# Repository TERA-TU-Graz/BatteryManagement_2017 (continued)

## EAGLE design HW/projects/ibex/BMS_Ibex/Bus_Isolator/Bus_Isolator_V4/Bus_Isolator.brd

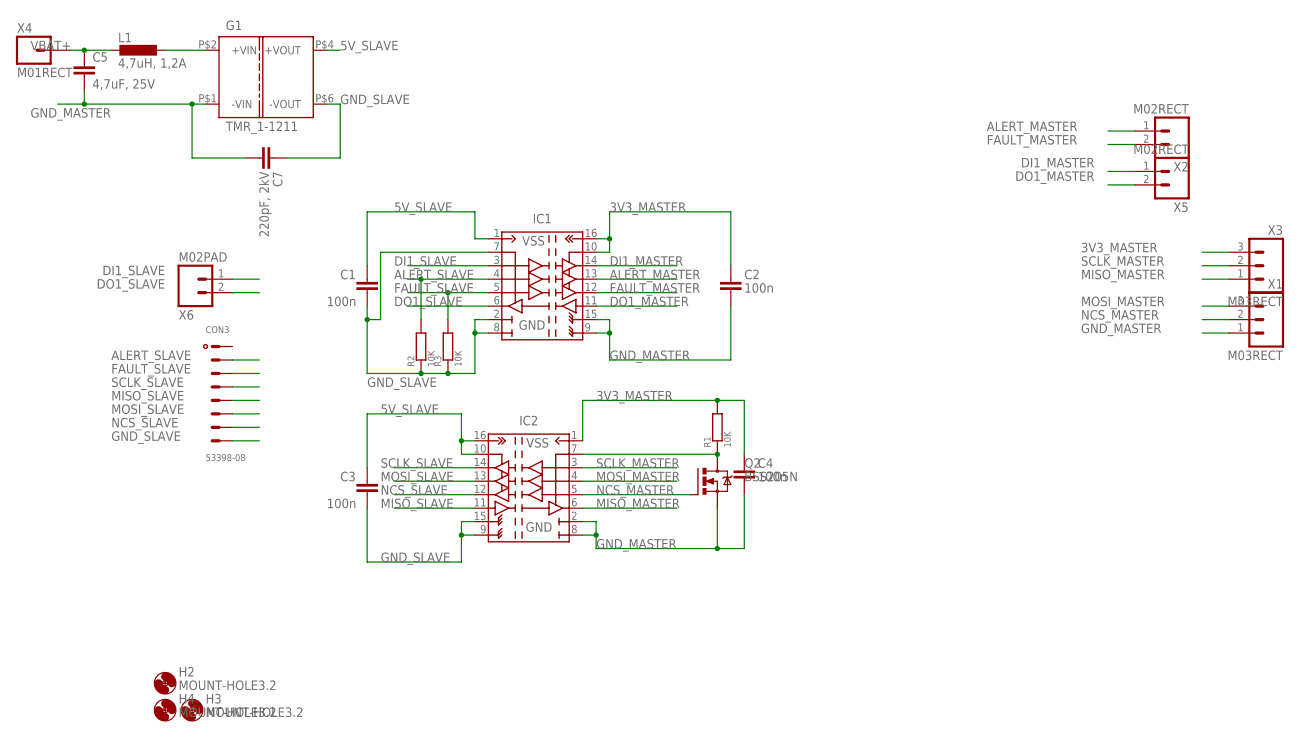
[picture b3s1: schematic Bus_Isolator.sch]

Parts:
C1, C2, C3, C4: 100n; C0805
C5: 4,7uF, 25V; C0805
C7: 220pF, 2kV; C1210_HV
CON3: 53398-08
G1: TMR_1-1211; TMR_1-??1?
H2, H3, H4: MOUNT-HOLE3.2; 3,2
IC1, IC2: ISO7241; R-PDSO-G16
L1: 4,7uH, 1,2A; L3225M
Q2: BSS205N; SOT23
R1: 10K; R0603
R2, R3: 10K; R0805
X1, X3: M03RECT; 1X03_RECT
X2, X5: M02RECT; 1X02_RECT
X4: M01RECT; 1X01_RECT
X6: M02PAD; 1X02

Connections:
3V3_MASTER: C2.2, C4.2, IC1.10 (EN2), IC1.16 (VCC2), IC2.1 (VCC1), R1.2, X3.3
5V_SLAVE: C1.2, C3.2, G1.P$4 (+VOUT), IC1.1 (VCC1), IC2.10 (EN2), IC2.16 (VCC2)
ALERT_MASTER: IC1.13 (OUT_B), X2.1
ALERT_SLAVE: CON3.2, IC1.4 (IN_B), R2.2
DI1_MASTER: IC1.14 (OUT_A), X5.1
DI1_SLAVE: IC1.3 (IN_A), X6.1
DO1_MASTER: IC1.11 (IN_D), X5.2
DO1_SLAVE: IC1.6 (OUT_D), X6.2
FAULT_MASTER: IC1.12 (OUT_C), X2.2
FAULT_SLAVE: CON3.3, IC1.5 (IN_C), R3.2
GND_MASTER: C2.1, C4.1, C5.2, C7.P$1 (1), G1.P$1 (-VIN), IC1.9 (GND22), IC1.15 (GND21), IC2.2 (GND11), IC2.8 (GND12), Q2.2 (S), X1.1
GND_SLAVE: C1.1, C3.1, C7.P$2 (2), CON3.8, G1.P$6 (-VOUT), IC1.2 (GND11), IC1.7 (EN1), IC1.8 (GND12), IC2.9 (GND22), IC2.15 (GND21), R2.1, R3.1
MISO_MASTER: IC2.6 (OUT_D), X3.1
MISO_SLAVE: CON3.5, IC2.11 (IN_D)
MOSI_MASTER: IC2.4 (IN_B), X1.3
MOSI_SLAVE: CON3.6, IC2.13 (OUT_B)
unnamed: IC2.7 (EN1), Q2.3 (D), R1.1
unnamed: G1.P$2 (+VIN), L1.1
NCS_MASTER: IC2.5 (IN_C), Q2.1 (G), X1.2
NCS_SLAVE: CON3.7, IC2.12 (OUT_C)
SCLK_MASTER: IC2.3 (IN_A), X3.2
SCLK_SLAVE: CON3.4, IC2.14 (OUT_A)
VBAT+: C5.1, L1.2, X4.1

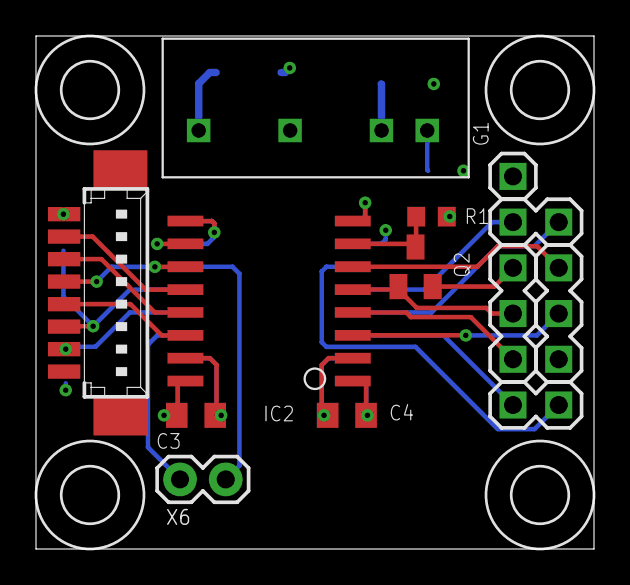
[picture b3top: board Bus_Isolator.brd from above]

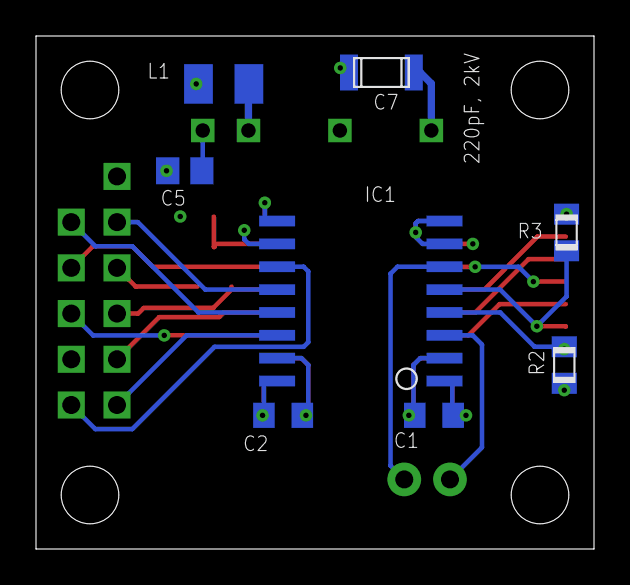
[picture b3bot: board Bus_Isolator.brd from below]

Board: 4 copper layers, 31.0 x 28.5 mm, 25 parts (8 on the bottom side), 23 nets.

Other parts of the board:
H1: MOUNT-HOLE3.2; 3,2

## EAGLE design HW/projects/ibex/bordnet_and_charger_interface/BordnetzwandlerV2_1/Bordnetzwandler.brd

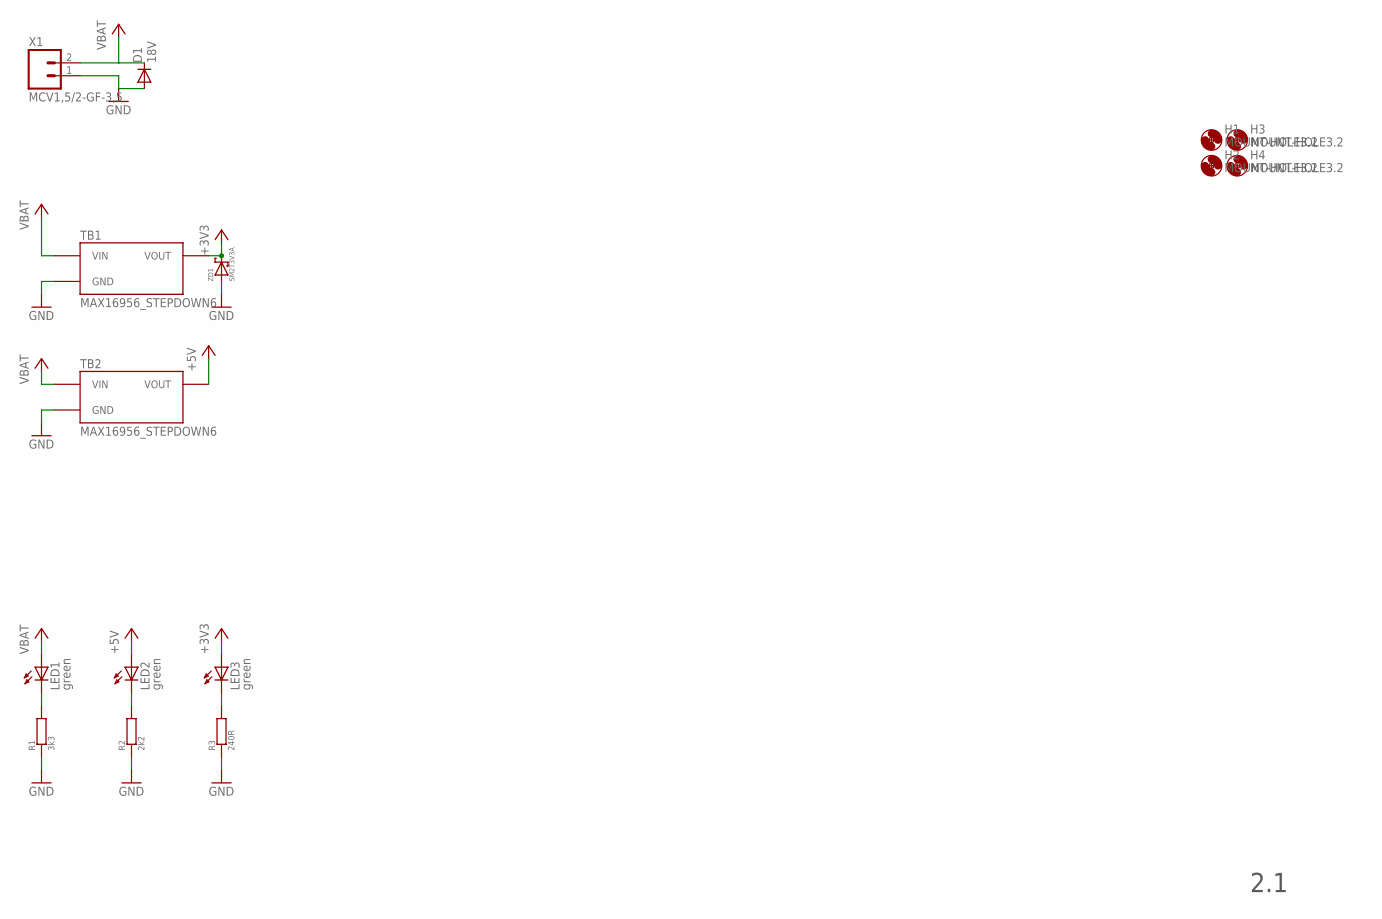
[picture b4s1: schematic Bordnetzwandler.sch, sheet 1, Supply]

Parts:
D1: 18V; DO214AA
H1, H2, H3, H4: MOUNT-HOLE3.2; 3,2
LED1, LED2, LED3: green; CHIP-LED0805
R1: 3k3; R0805
R2: 2k2; R0805
R3: 240R; R0805
TB1, TB2: MAX16956_STEPDOWN6
X1: MCV1,5/2-GF-3,5
ZD1: SM2T3V3A

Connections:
+3V3: LED3.A, TB1.VOUT, ZD1.P$2; also elsewhere on the board
+5V: LED2.A, TB2.VOUT; also elsewhere on the board
GND: D1.A, R1.1, R2.1, R3.1, TB1.GND, TB1.GND2 (GND), TB2.GND, TB2.GND2 (GND), X1.1, ZD1.P$1, ZD1.P$11; also elsewhere on the board
unnamed: LED2.C, R2.2
unnamed: LED3.C, R3.2
unnamed: LED1.C, R1.2
VBAT: D1.C, LED1.A, TB1.VIN, TB2.VIN, X1.2; also elsewhere on the board

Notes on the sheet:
2.1

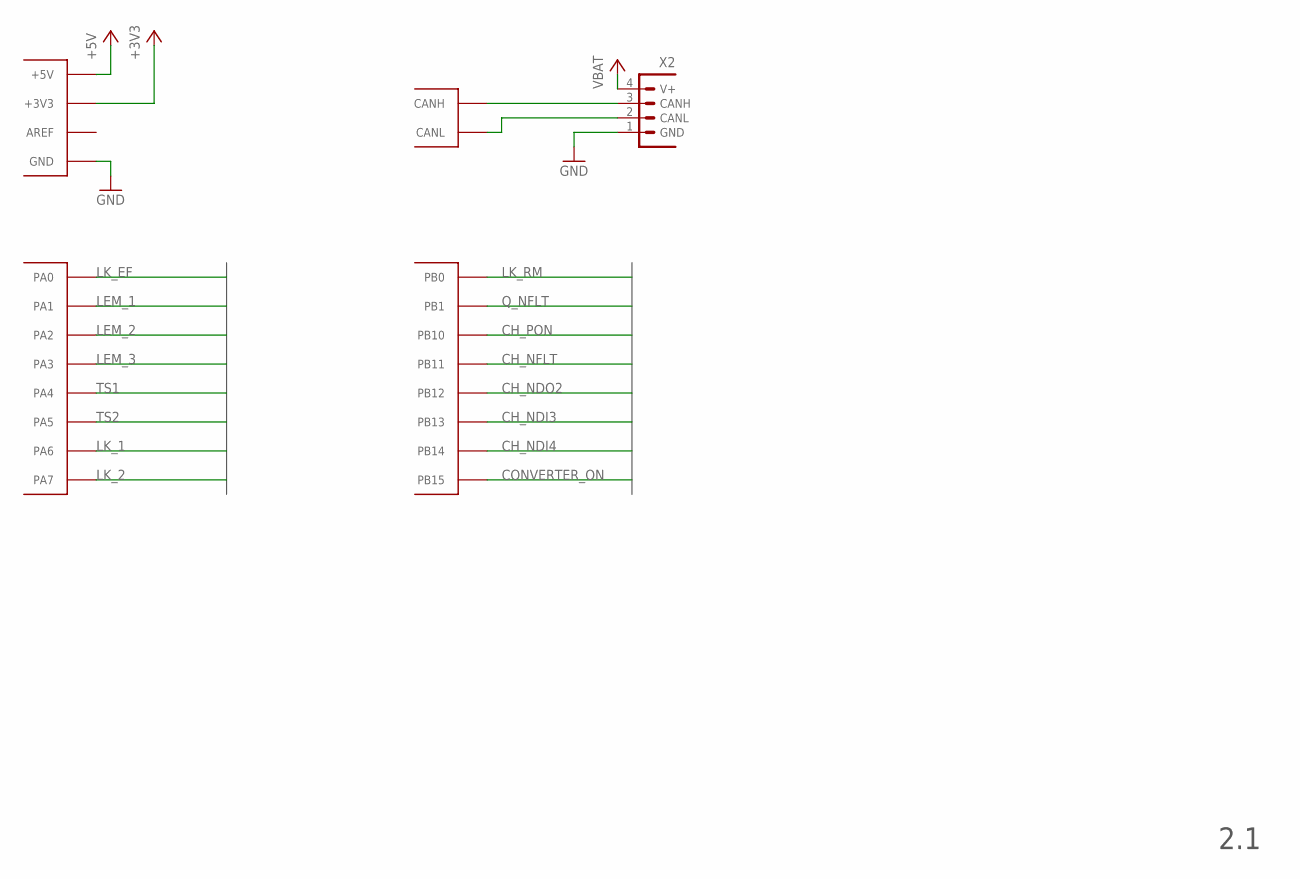
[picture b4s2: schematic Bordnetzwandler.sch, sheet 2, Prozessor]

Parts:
CANIO_1: STM32F103XX_CAN-IO-EXPANDER; STM32F103XX_CANIO-EXPANDER
X2: CIOC_4-1-FV-A_CAN-BELEGUNG; CIOC_4-1-FV

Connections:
+3V3: CANIO_1.VCC (+3V3); also elsewhere on the board
+5V: CANIO_1.+5V; also elsewhere on the board
CAN1_H: CANIO_1.CANH, X2.3 (CANH)
CAN1_L: CANIO_1.CANL, X2.2 (CANL)
CH_NDI3: CANIO_1.PB13; also elsewhere on the board
CH_NDI4: CANIO_1.PB14; also elsewhere on the board
CH_NDO2: CANIO_1.PB12; also elsewhere on the board
CH_NFLT: CANIO_1.PB11; also elsewhere on the board
CH_PON: CANIO_1.PB10; also elsewhere on the board
CONVERTER_ON: CANIO_1.PB15; also elsewhere on the board
GND: CANIO_1.GND1 (GND), X2.1 (GND); also elsewhere on the board
LEM_1: CANIO_1.PA1; also elsewhere on the board
LEM_2: CANIO_1.PA2; also elsewhere on the board
LEM_3: CANIO_1.PA3; also elsewhere on the board
LK_1: CANIO_1.PA6; also elsewhere on the board
LK_2: CANIO_1.PA7; also elsewhere on the board
LK_EF: CANIO_1.PA0; also elsewhere on the board
LK_RM: CANIO_1.PB0; also elsewhere on the board
Q_NFLT: CANIO_1.PB1; also elsewhere on the board
TS1: CANIO_1.PA4; also elsewhere on the board
TS2: CANIO_1.PA5; also elsewhere on the board
VBAT: X2.4 (V+); also elsewhere on the board

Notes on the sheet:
2.1

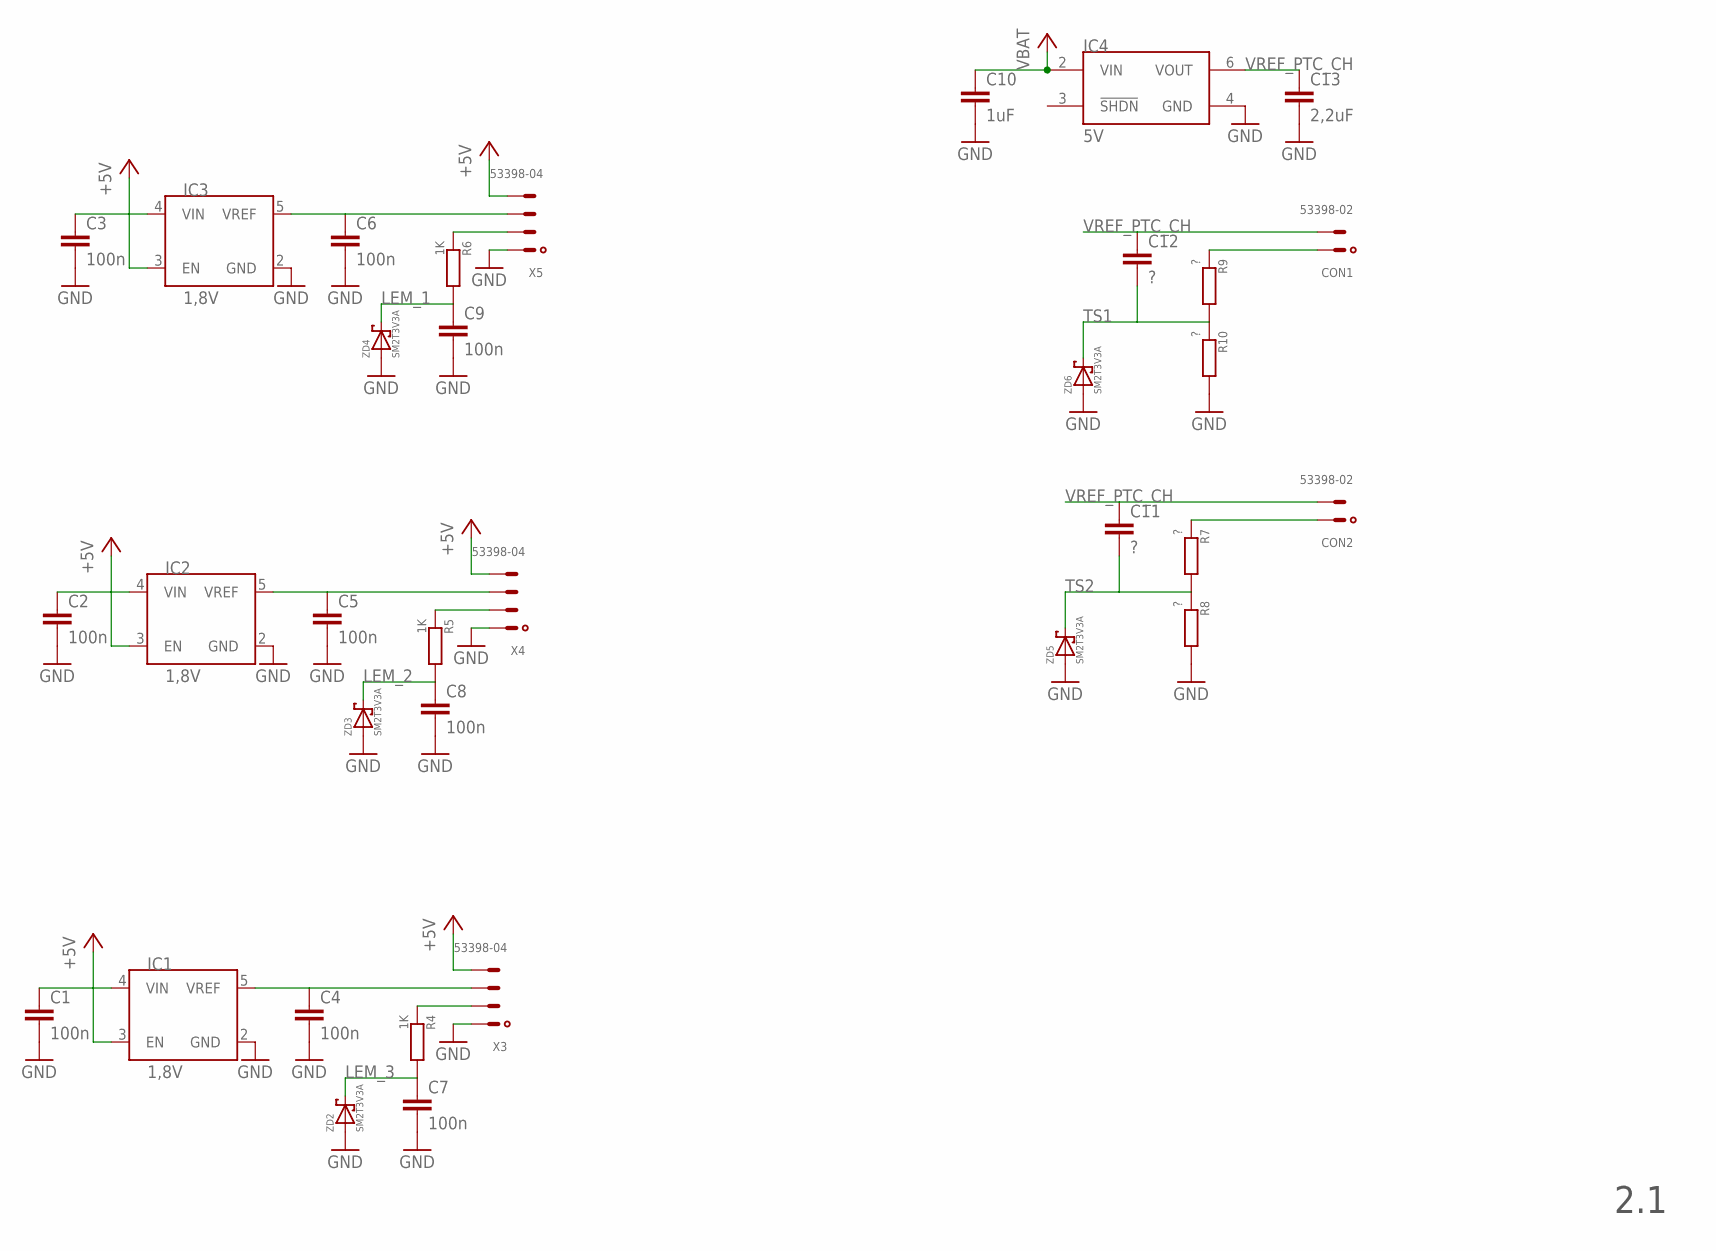
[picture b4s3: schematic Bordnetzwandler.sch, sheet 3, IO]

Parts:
C1, C2, C3, C4, C5, C6, C7, C8, C9: 100n; C0805
C10: 1uF; C0805
C11, C12: ?; C0805
C13: 2,2uF; C0805
CON1, CON2: 53398-02
IC1, IC2, IC3: 1,8V; SOT23-5L
IC4: 5V; SO08
R4, R5, R6: 1K; R0805
R7, R8, R9, R10: ?; R0805
X3, X4, X5: 53398-04
ZD2, ZD3, ZD4, ZD5, ZD6: SM2T3V3A

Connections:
+5V: C1.1, C2.1, C3.1, IC1.3 (EN), IC1.4 (VIN), IC2.3 (EN), IC2.4 (VIN), IC3.3 (EN), IC3.4 (VIN), X3.4, X4.4, X5.4; also elsewhere on the board
GND: C1.2, C2.2, C3.2, C4.2, C5.2, C6.2, C7.2, C8.2, C9.2, C10.2, C13.2, IC1.2 (GND), IC2.2 (GND), IC3.2 (GND), IC4.4 (GND), R8.2, R10.2, X3.1, X4.1, X5.1, ZD2.P$1, ZD2.P$11, ZD3.P$1, ZD3.P$11, ZD4.P$1, ZD4.P$11, ZD5.P$1, ZD5.P$11, ZD6.P$1, ZD6.P$11; also elsewhere on the board
LEM_1: C9.1, R6.2, ZD4.P$2; also elsewhere on the board
LEM_2: C8.1, R5.2, ZD3.P$2; also elsewhere on the board
LEM_3: C7.1, R4.2, ZD2.P$2; also elsewhere on the board
unnamed: C4.1, IC1.5 (VREF), X3.3
unnamed: R6.1, X5.2
unnamed: C5.1, IC2.5 (VREF), X4.3
unnamed: CON1.1, R9.1
unnamed: R5.1, X4.2
unnamed: C6.1, IC3.5 (VREF), X5.3
unnamed: R4.1, X3.2
unnamed: CON2.1, R7.1
TS1: C12.2, R9.2, R10.1, ZD6.P$2; also elsewhere on the board
TS2: C11.2, R7.2, R8.1, ZD5.P$2; also elsewhere on the board
VBAT: C10.1, IC4.2 (VIN); also elsewhere on the board
VREF_PTC_CH: C11.1, C12.1, C13.1, CON1.2, CON2.2, IC4.6 (VOUT)

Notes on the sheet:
2.1

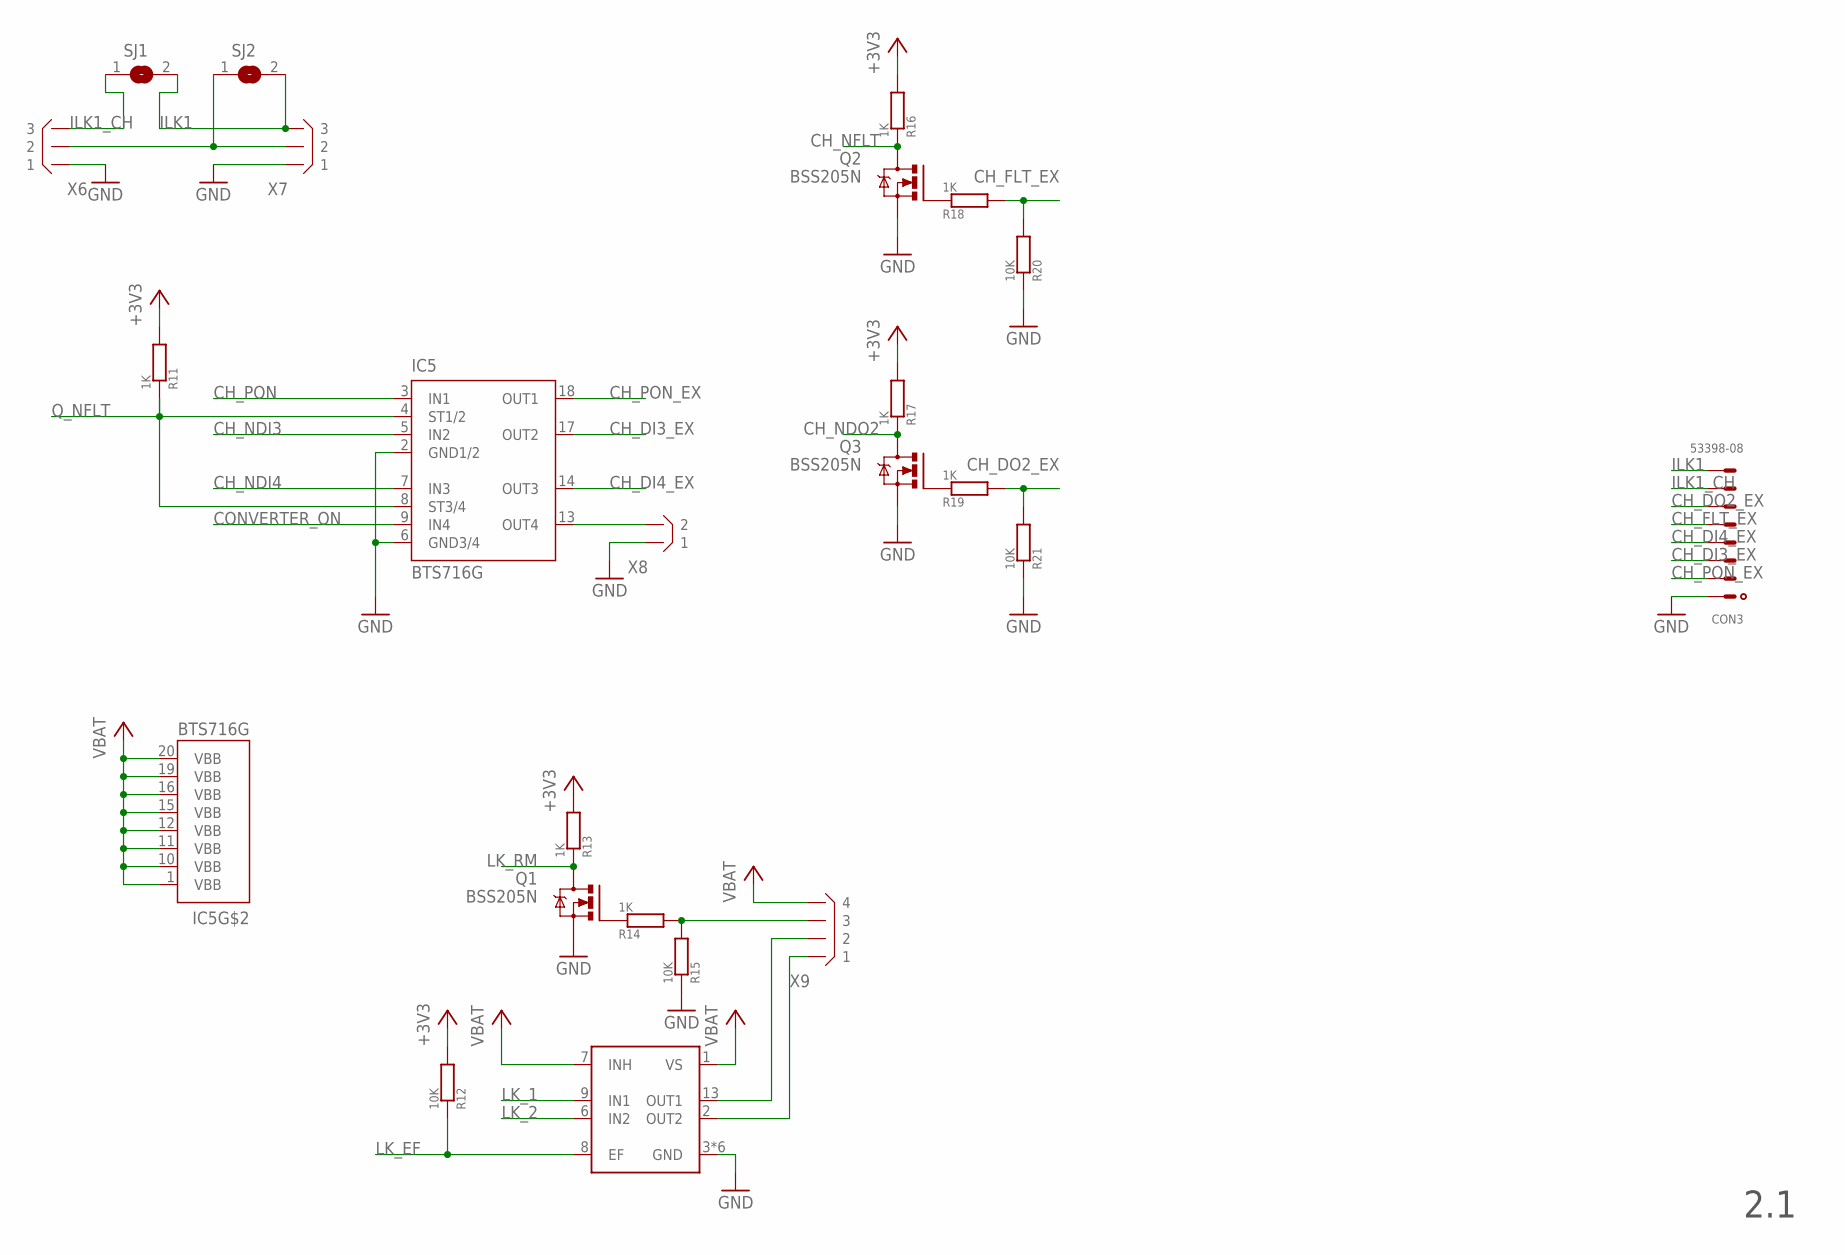
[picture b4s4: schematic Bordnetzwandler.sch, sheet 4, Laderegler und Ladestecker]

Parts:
CON3: 53398-08
IC5: BTS716G; PG-DSO-20
IC6: TLE4207GN; INF-PG-DSO-14-22_N_1PRIMARY
Q1, Q2, Q3: BSS205N; SOT23
R11, R16, R17, R18, R19: 1K; R0603
R12, R15: 10K; R0805
R13, R14: 1K; R0805
R20, R21: 10K; R0603
SJ1, SJ2: SJ
X6, X7: B3B-XH
X8: B2B-XH
X9: B4B-XH

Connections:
+3V3: R11.2, R12.2, R13.2, R16.2, R17.2; also elsewhere on the board
CH_DI3_EX: CON3.3, IC5.17 (OUT2)
CH_DI4_EX: CON3.4, IC5.14 (OUT3)
CH_DO2_EX: CON3.6, R19.2, R21.2
CH_FLT_EX: CON3.5, R18.2, R20.2
CH_NDI3: IC5.5 (IN2); also elsewhere on the board
CH_NDI4: IC5.7 (IN3); also elsewhere on the board
CH_NDO2: Q3.3 (D), R17.1; also elsewhere on the board
CH_NFLT: Q2.3 (D), R16.1; also elsewhere on the board
CH_PON: IC5.3 (IN1); also elsewhere on the board
CH_PON_EX: CON3.2, IC5.18 (OUT1)
CONVERTER_ON: IC5.9 (IN4); also elsewhere on the board
GND: CON3.1, IC5.2 (GND1/2), IC5.6 (GND3/4), IC6.3 (GND), IC6.4 (GND), IC6.5 (GND), IC6.10 (GND), IC6.11 (GND), IC6.12 (GND), Q1.2 (S), Q2.2 (S), Q3.2 (S), R15.1, R20.1, R21.1, X6.P$1 (1), X7.P$1 (1), X8.P$1 (1); also elsewhere on the board
ILK1: CON3.8, SJ1.2, SJ2.2, X7.P$3 (3)
ILK1_CH: CON3.7, SJ1.1, X6.P$3 (3)
ILK2: SJ2.1, X6.P$2 (2), X7.P$2 (2)
LK_1: IC6.9 (IN1); also elsewhere on the board
LK_2: IC6.6 (IN2); also elsewhere on the board
LK_EF: IC6.8 (EF), R12.1; also elsewhere on the board
LK_RM: Q1.3 (D), R13.1; also elsewhere on the board
unnamed: IC5.13 (OUT4), X8.P$2 (2)
unnamed: Q3.1 (G), R19.1
unnamed: Q1.1 (G), R14.1
unnamed: R14.2, R15.2, X9.P$3 (3)
unnamed: IC6.13 (OUT1), X9.P$2 (2)
unnamed: IC6.2 (OUT2), X9.P$1 (1)
unnamed: Q2.1 (G), R18.1
Q_NFLT: IC5.4 (ST1/2), IC5.8 (ST3/4), R11.1; also elsewhere on the board
VBAT: IC5.1 (VBB), IC5.10 (VBB), IC5.11 (VBB), IC5.12 (VBB), IC5.15 (VBB), IC5.16 (VBB), IC5.19 (VBB), IC5.20 (VBB), IC6.1 (VS), IC6.7 (INH), X9.P$4 (4); also elsewhere on the board

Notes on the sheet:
2.1

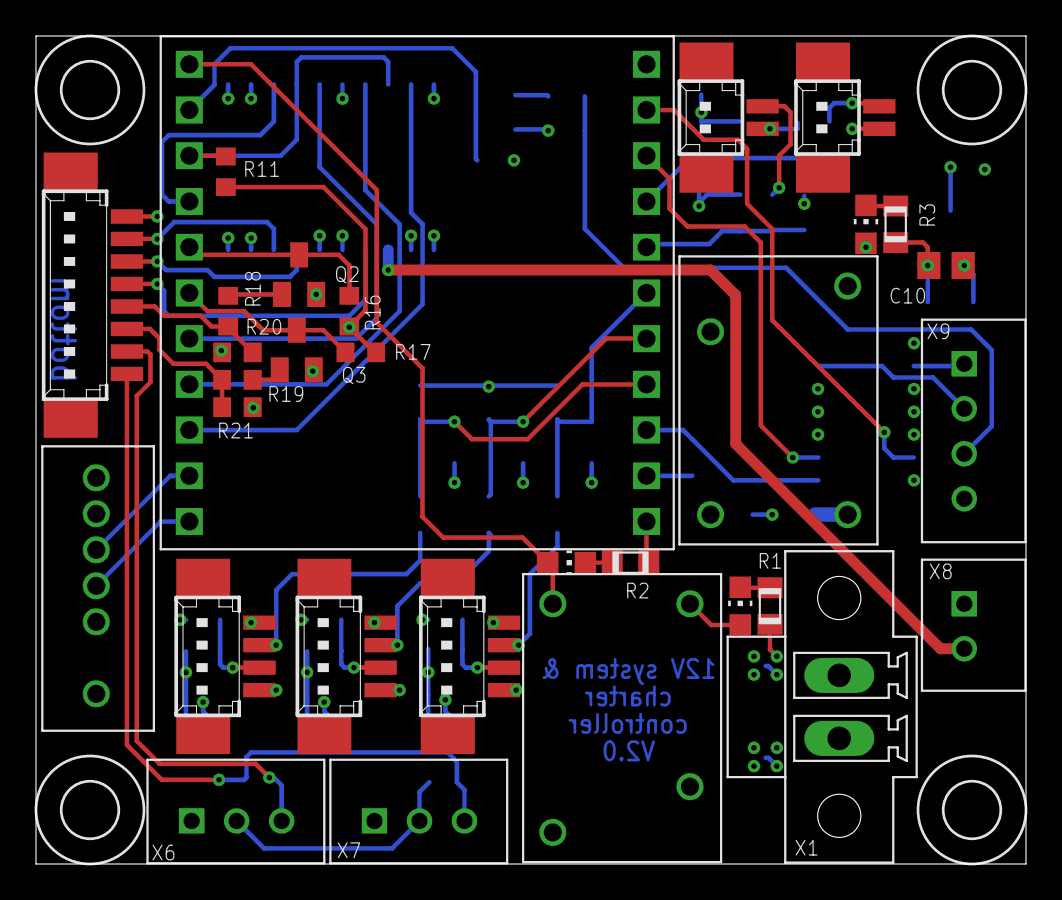
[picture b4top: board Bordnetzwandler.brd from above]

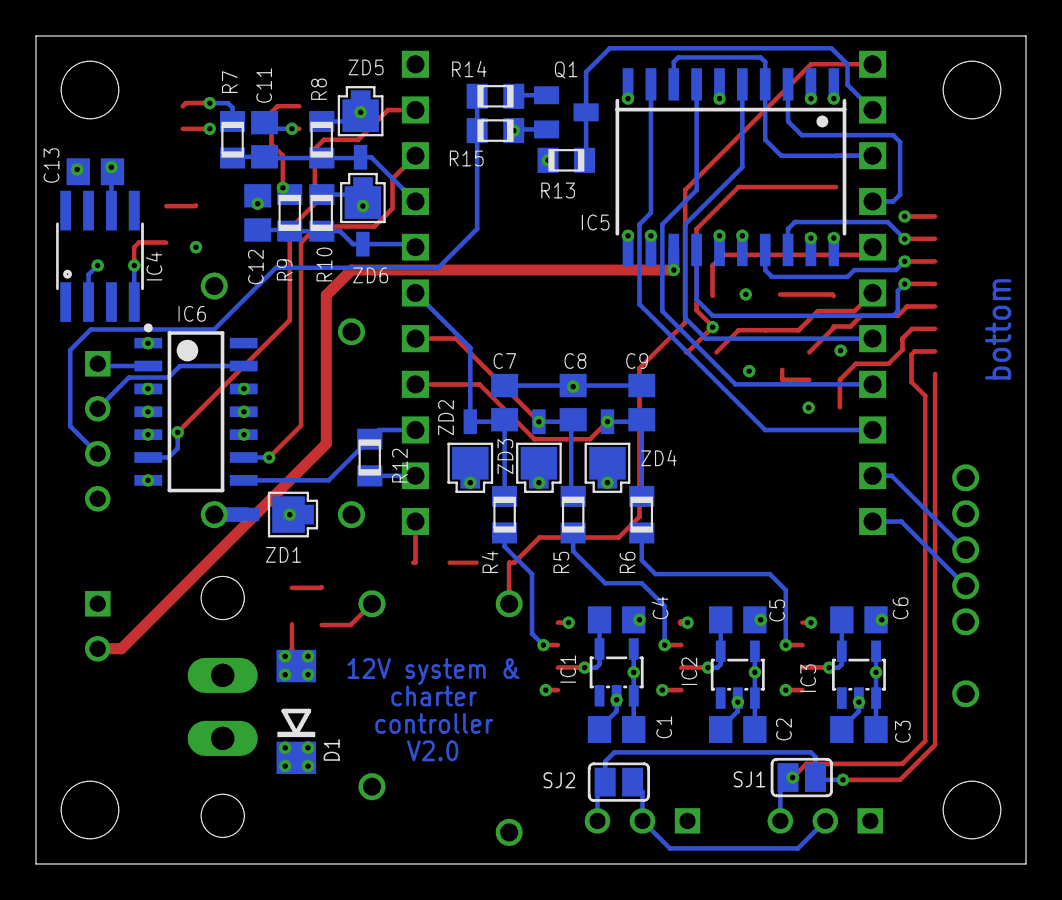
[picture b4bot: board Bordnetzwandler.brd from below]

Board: 4 copper layers, 55.0 x 46.0 mm, 74 parts (39 on the bottom side), 49 nets.

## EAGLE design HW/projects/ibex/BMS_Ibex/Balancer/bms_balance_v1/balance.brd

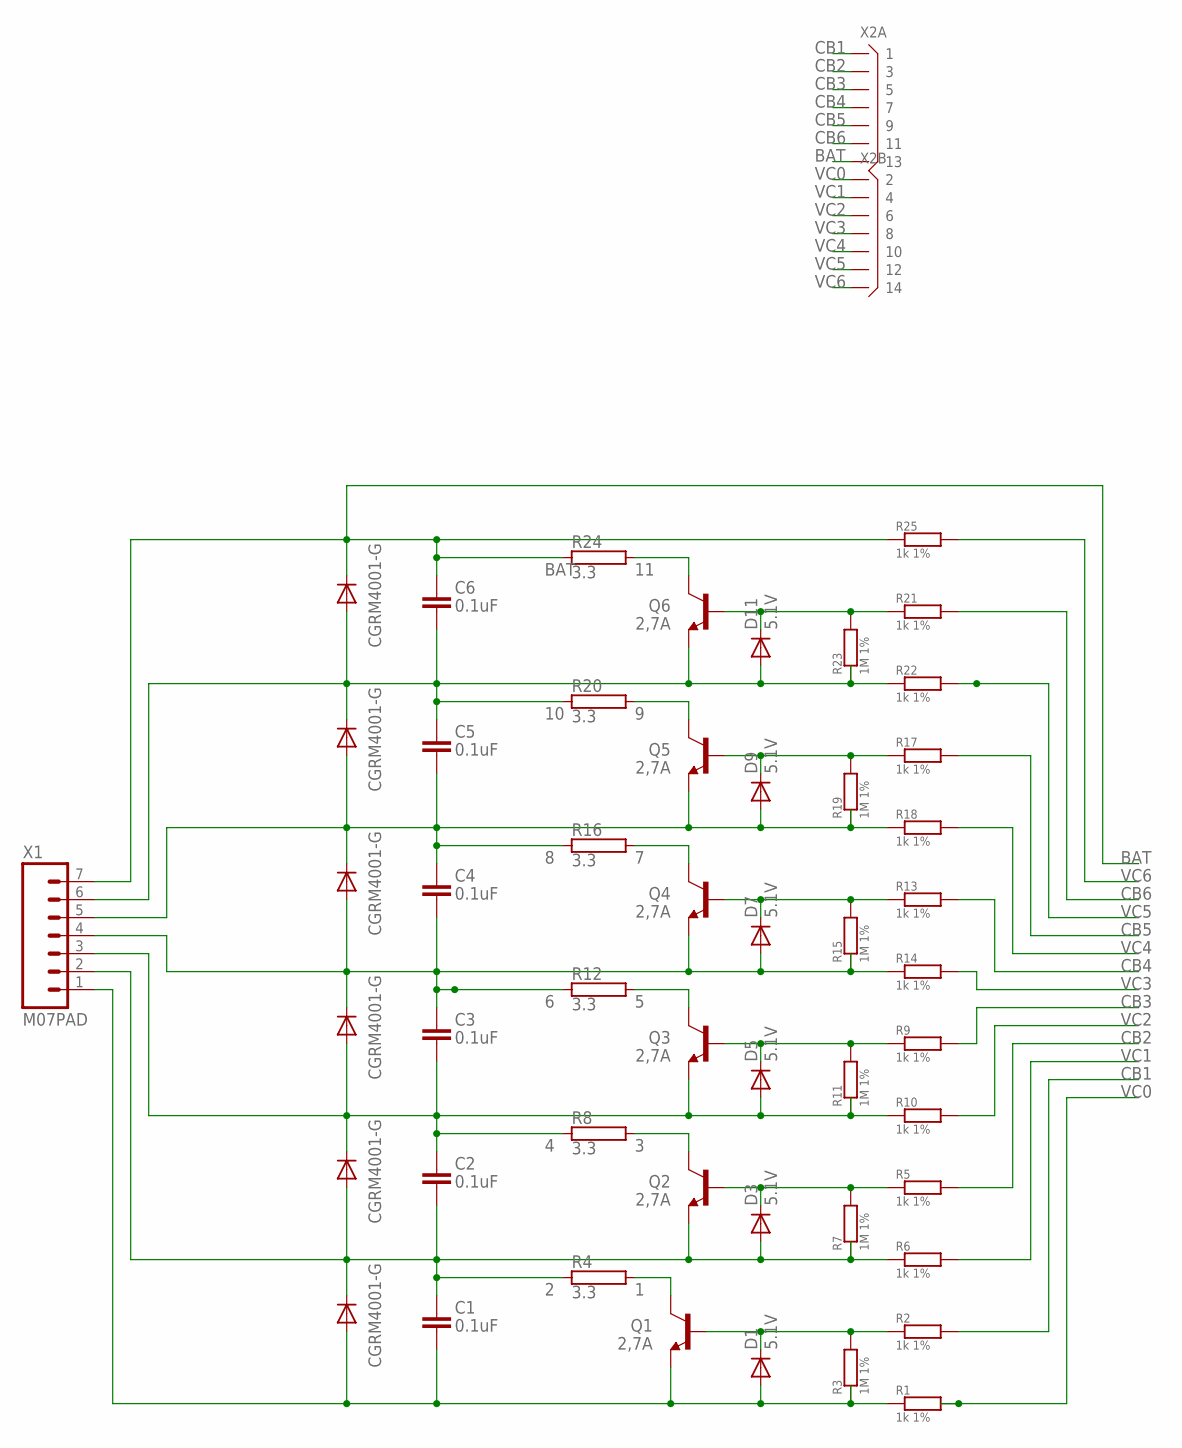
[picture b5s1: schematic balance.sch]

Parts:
C1, C2, C3, C4, C5, C6: 0.1uF; C0805
D1, D3, D5, D7, D9, D11: 5.1V; SOD-323
D2, D4, D6, D8, D10, D12: CGRM4001-G; SOD-123_MINI-SMA
Q1, Q2, Q3, Q4, Q5, Q6: 2,7A; SOT23
R1, R2, R5, R6, R9, R10, R13, R14, R17, R18, R21, R22, R25: 1k 1%; R0805
R3, R7, R11, R15, R19, R23: 1M 1%; R0805
R4, R8, R12, R16, R20, R24: 3.3; HS15
X1: M07PAD; 1X07
X2: X07X2IR; X14R-IDC

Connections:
1: Q1.3 (C), R4.2
2: C1.2, C2.1, D2.C, D3.2 (A), D4.A, Q2.2 (E), R4.1, R6.1, R7.1, X1.2
3: Q2.3 (C), R8.2
4: C2.2, C3.1, D4.C, D5.2 (A), D6.A, Q3.2 (E), R8.1, R10.1, R11.1, X1.3
5: Q3.3 (C), R12.2
6: C3.2, C4.1, D6.C, D7.2 (A), D8.A, Q4.2 (E), R12.1, R14.1, R15.1, X1.4
7: Q4.3 (C), R16.2
8: C4.2, C5.1, D8.C, D9.2 (A), D10.A, Q5.2 (E), R16.1, R18.1, R19.1, X1.5
9: Q5.3 (C), R20.2
10: C5.2, C6.1, D10.C, D11.2 (A), D12.A, Q6.2 (E), R20.1, R22.1, R23.1, X1.6
11: Q6.3 (C), R24.2
BAT: C6.2, D12.C, R24.1, R25.1, X1.7, X2.13
CB1: R2.2, X2.1
CB2: R5.2, X2.3
CB3: R9.2, X2.5
CB4: R13.2, X2.7
CB5: R17.2, X2.9
CB6: R21.2, X2.11
unnamed: D1.1 (C), Q1.1 (B), R2.1, R3.2
unnamed: D3.1 (C), Q2.1 (B), R5.1, R7.2
unnamed: D5.1 (C), Q3.1 (B), R9.1, R11.2
unnamed: D7.1 (C), Q4.1 (B), R13.1, R15.2
unnamed: D9.1 (C), Q5.1 (B), R17.1, R19.2
unnamed: D11.1 (C), Q6.1 (B), R21.1, R23.2
unnamed: C1.1, D1.2 (A), D2.A, Q1.2 (E), R1.1, R3.1, X1.1
VC0: R1.2, X2.2
VC1: R6.2, X2.4
VC2: R10.2, X2.6
VC3: R14.2, X2.8
VC4: R18.2, X2.10
VC5: R22.2, X2.12
VC6: R25.2, X2.14

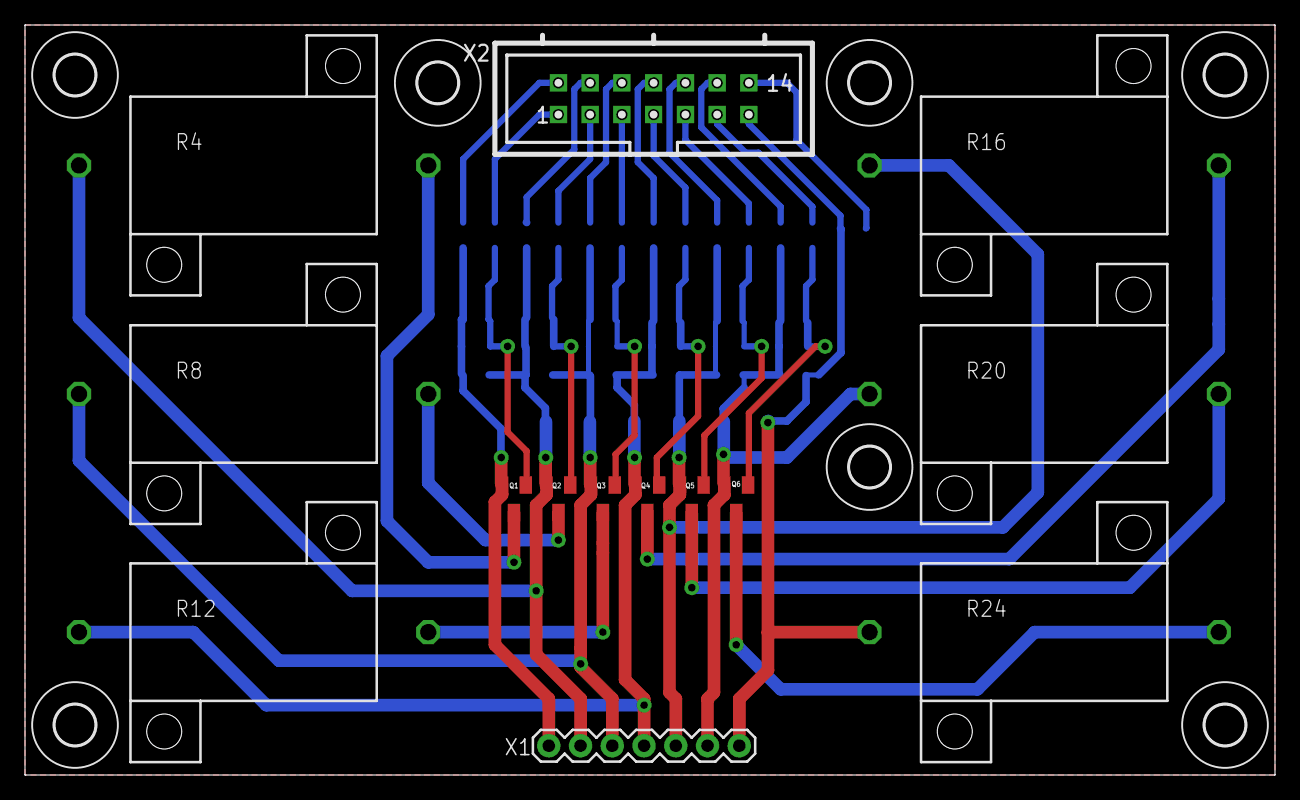
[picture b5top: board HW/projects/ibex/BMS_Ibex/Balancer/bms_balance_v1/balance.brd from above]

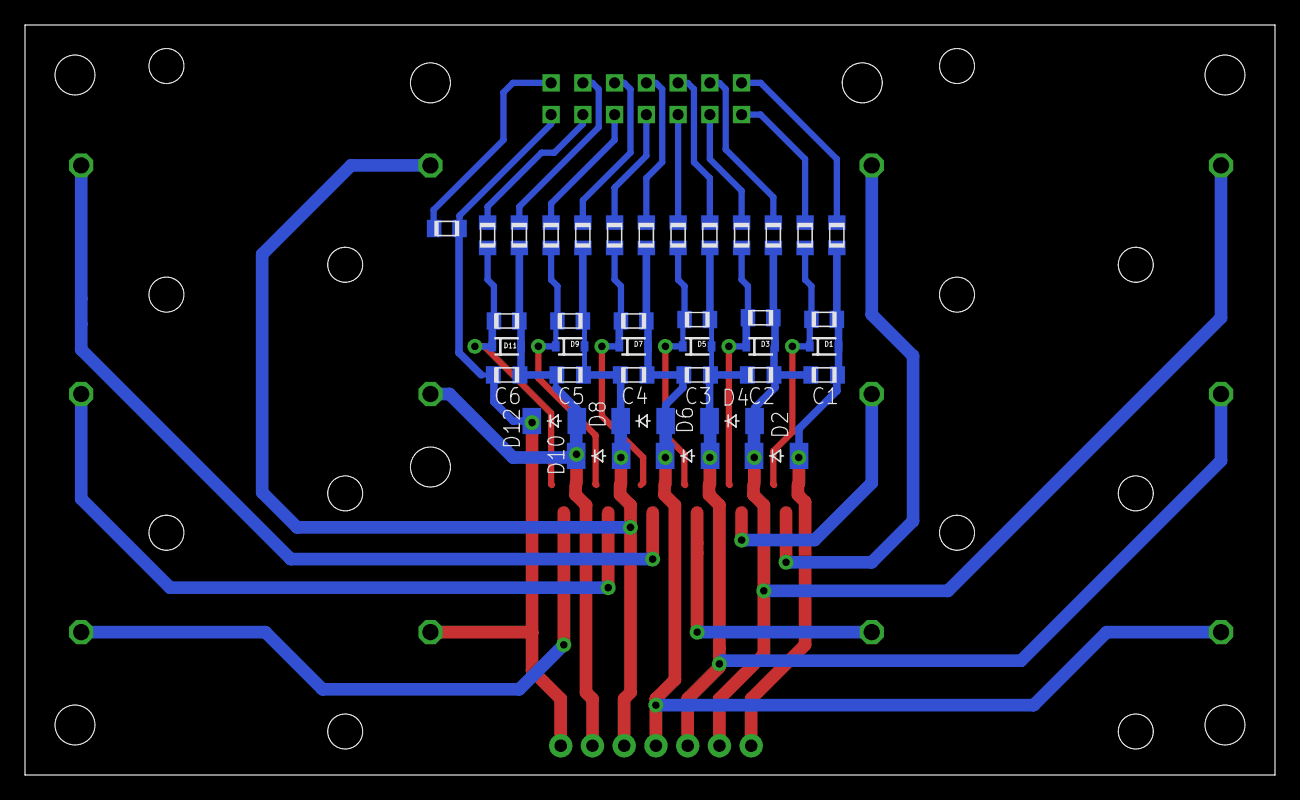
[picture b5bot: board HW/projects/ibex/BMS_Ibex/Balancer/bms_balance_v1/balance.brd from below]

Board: 4 copper layers, 100.0 x 60.0 mm, 58 parts (37 on the bottom side), 32 nets.

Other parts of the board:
U$1, U$2, U$3, U$4, U$5, U$6, U$7: 3,2

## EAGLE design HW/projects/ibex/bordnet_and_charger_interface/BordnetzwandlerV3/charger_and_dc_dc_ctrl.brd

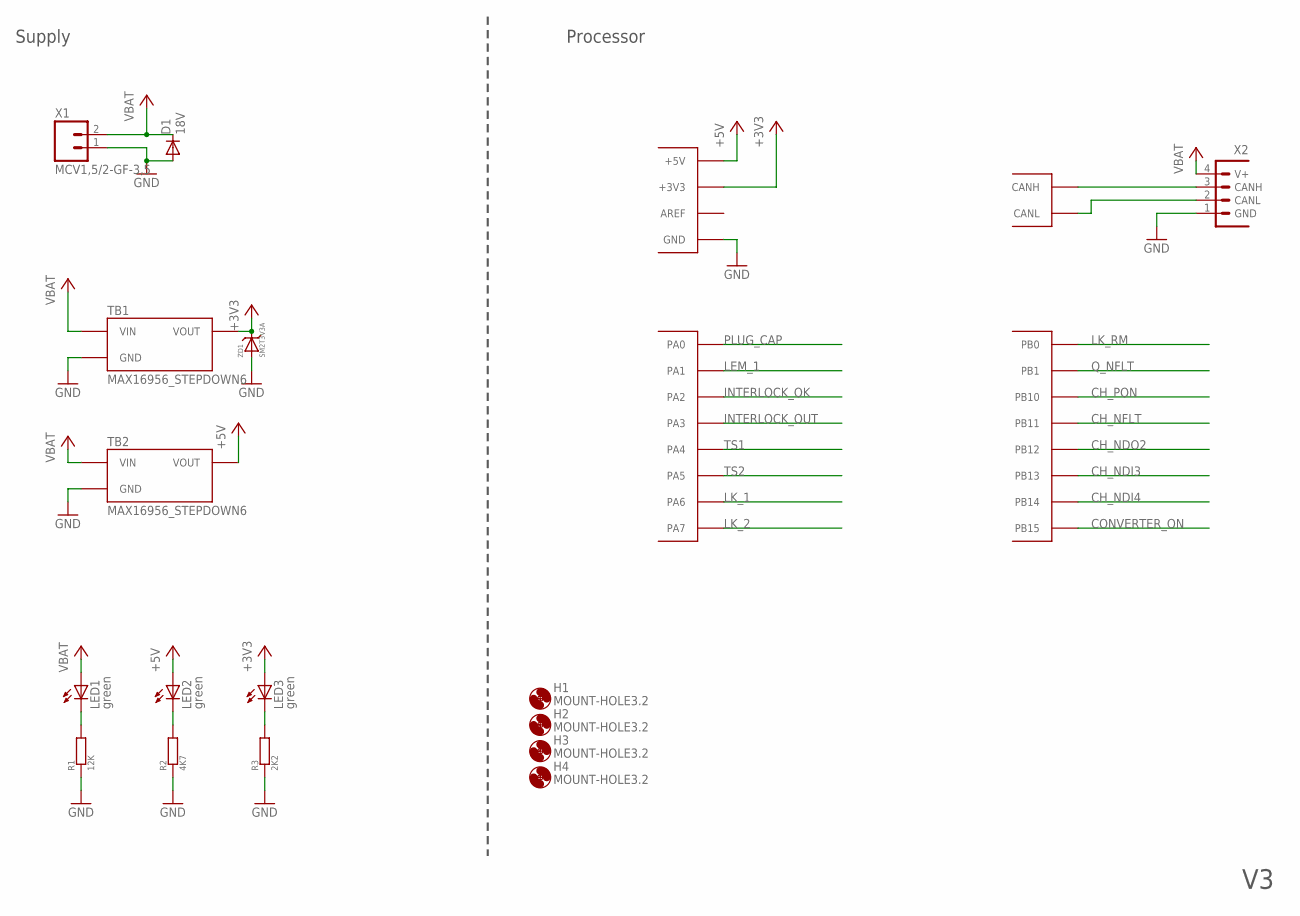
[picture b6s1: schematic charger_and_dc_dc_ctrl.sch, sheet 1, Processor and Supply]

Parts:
CANIO_1: STM32F103XX_CAN-IO-EXPANDERC; STM32F103XX_CANIO-EXPANDER3
D1: 18V; DO214AA
H1, H2, H3, H4: MOUNT-HOLE3.2; 3,2
LED1, LED2, LED3: green; CHIP-LED0805
R1: 12K; R0805
R2: 4K7; R0805
R3: 2K2; R0805
TB1, TB2: MAX16956_STEPDOWN6
X1: MCV1,5/2-GF-3,5
X2: CIOC_4-1-FV-A_CAN-BELEGUNG; CIOC_4-1-FV
ZD1: SM2T3V3A

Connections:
+3V3: CANIO_1.VCC (+3V3), LED3.A, TB1.VOUT, ZD1.P$2; also elsewhere on the board
+5V: CANIO_1.+5V, LED2.A, TB2.VOUT; also elsewhere on the board
CAN1_H: CANIO_1.CANH, X2.3 (CANH)
CAN1_L: CANIO_1.CANL, X2.2 (CANL)
CH_NDI3: CANIO_1.PB13; also elsewhere on the board
CH_NDI4: CANIO_1.PB14; also elsewhere on the board
CH_NDO2: CANIO_1.PB12; also elsewhere on the board
CH_NFLT: CANIO_1.PB11; also elsewhere on the board
CH_PON: CANIO_1.PB10; also elsewhere on the board
CONVERTER_ON: CANIO_1.PB15; also elsewhere on the board
GND: CANIO_1.GND1 (GND), D1.A, R1.1, R2.1, R3.1, TB1.GND, TB1.GND2 (GND), TB2.GND, TB2.GND2 (GND), X1.1, X2.1 (GND), ZD1.P$1, ZD1.P$11; also elsewhere on the board
INTERLOCK_OK: CANIO_1.PA2; also elsewhere on the board
INTERLOCK_OUT: CANIO_1.PA3; also elsewhere on the board
LEM_1: CANIO_1.PA1; also elsewhere on the board
LK_1: CANIO_1.PA6; also elsewhere on the board
LK_2: CANIO_1.PA7; also elsewhere on the board
LK_RM: CANIO_1.PB0; also elsewhere on the board
unnamed: LED2.C, R2.2
unnamed: LED3.C, R3.2
unnamed: LED1.C, R1.2
PLUG_CAP: CANIO_1.PA0; also elsewhere on the board
Q_NFLT: CANIO_1.PB1; also elsewhere on the board
TS1: CANIO_1.PA4; also elsewhere on the board
TS2: CANIO_1.PA5; also elsewhere on the board
VBAT: D1.C, LED1.A, TB1.VIN, TB2.VIN, X1.2, X2.4 (V+); also elsewhere on the board

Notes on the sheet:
Supply
Processor
